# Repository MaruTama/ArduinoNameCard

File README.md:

# Arduino Name(Business) Card

[日本版 READE](./README_JP.md)  
This is a template with Arduino uno compatibility board.  
It is only one master, it is created with a business card size of 91 x 55 mm.  

If you wanna create as panelized boards, see the [twoBoards branch](https://github.com/MaruTama/ArduinoNameCard/tree/twoBoards) .  

This was written sample code(blink) with board.

# Environment version
- KiCad 5.0.0
- ArduinoIDE 1.8.2
- GIMP 2.8
- Ubuntu 16.04 and macOS High Sierra (my environment)

Basically, ArduinoIDE, KiCad, GIMP are cross-platform and do not depend on OS.  

# Environment construction method
## Installation of Arduino IDE
### windows
It is recommended to install with Chocolatey.  
because since installer took time to download from the official site.  

Installation of Chocolatey
["Chocolateyを使った環境構築の時のメモ"](https://qiita.com/konta220/items/95b40b4647a737cb51aa)
 please refer above.  

To open cmd or PowerShell with administrator privileges.  

```
> Chocolate Upgrade Chocolate
> Chocolate installation arduino
```

It is OK to response "Yes" that the question comes twice.  

Install the All drivers for Arduino.  

### Mac
Mac is using brew to install Arduino IDE

```
brew cask install arduino
```

### Ubuntu
["Here"](https://www.arduino.cc/en/Main/Software), download the latest Linux 32 or 64. zip.  
The installation method when downloaded file is arduino-1.8.2-linux64.tar.xz.  

```
$ sudo tar -Jxvf arduino-1.8.2-linux64.tar.xz -C /usr/share
$ cd /usr/share
$ sudo mv arduino-1.8.2/ arduino
# Create a symbolic link.
$ sudo ln -s /usr/share/arduino/arduino /usr/local/bin/arduino
# 実行
$ arduino
# Run it with administrator privileges when if you can not use the port.
$ sudo arduino
```

## Installation Kicad
### windows
#### Install with choco
To install with choco, execute the following commands.  

```
> choco upgrade chocolatey
> choco install kicad
```

### Install with Installer
If you are installing using the installer, download the installer from the official website below.  
[http://kicad-pcb.org/download/windows/](http://kicad-pcb.org/download/windows/)  

### Mac
If you are installing using the installer, download the installer from the official website below.  
"KiCad main package" is what component files puts the library in github.  
"KiCad extras" is what the component files puts the library in local directory.  
[http://kicad-pcb.org/download/osx/](http://kicad-pcb.org/download/osx/)  

### ubuntu
Execute the following commands.  

```
$ sudo add-apt-repository --yes ppa:js-reynaud/kicad-4
$ sudo apt update
$ sudo apt install kicad
```

## Setting of Kicad
### Component library
The component library is "~. Lib file".  
And each component is included in the file.  

Container Nebraska Pass

| Component library files | User defind search path |
|:------------|:--------------|
| res/lib/ArduinoNameCard.lib | res/lib |

### Footprint Library
The footprint library is a folder as a "~.Pretty".  
And contains the file ".kicad_mod" of each part footprint.  

Footprint library path  

| nickname | path |
|:------------|:--------------|
| ArduinoNameCard | ${KIPRJMOD}/res/lib/ArduinoNameCard.pretty |

### kicad library

Basically chip parts are unified to the following sizes.  

|   EIA  |   JIS  |
|:-------|:-------|
| 0805 | 2012 |

["Quick KICAD Library Component Builder"](http://kicad.rohrbacher.net/quicklib.php)
FT232RL.lib was created with above that using website.  

The ATMEGA 328-AU library was downloaded from ["here"](https://www.snapeda.com/parts/ATMEGA328-AU/Atmel/view-part/)

# # Build Arduino Name cards
Create a PCB footprint from the image.

### 1. Create an image according to the size of the free space on the Name Card
Create new image that using gimp.
Set about 1000dpi.  

The image used this time is put in [./res/img/origin](https://github.com/MaruTama/ArduinoNameCard/tree/master/res/img/origin) of the repository.
Please use this.  

Each image is supposed to write the following things.  
- affiliation.png -> affiliation
- name.png -> name
- address.png -> contact information

### 2. Enter pictures and characters in the picture
As an example, let's write the name in name.png.  
Binarize the image when if in case color image. -> 3  

### 3. I will make a black character white character
You need color turn when it's a white background and black character that  using gimp.  
how to turn color.  
menu -> "colors" -> "Inverted".  

### 4. Create a footprint
You can choose **silk** or **copper** what information to be placed on the board.  
If you put it in silk it will look like affiliation.png in the figure below.  
If it is copper, it will be like name.png and address.png.  

Start "bimmpa to component".  

To create a silk -> to 5  
To create a copper → to 6

### 5. Create with silk
Click "Load bitmap".  
As an example this time, I read name.png.  
Check sure the resolution is about 1000 dpi.  

Check "Front silk screen".  
Click "Export" after to generate output the filename.  
set name of output file as a name_silk.kicad_mod.  

### 6. Create with copper
Click "Load bitmap".  
As an example this time, I read name.png.  
Check sure the resolution is about 1000 dpi.  

Check "Front solder mask".  
Click "Export" after to generate output the filename.  
set name of output file as a name_mask.kicad_mod.   

Process the output footprint of name_mask.kicad_mod.  
In we will make that using the resist mask and the copper.  

The script is written in Python.  
A script is placed in [./python/main.py](https://github.com/MaruTama/ArduinoNameCard/blob/master/python/main.py) in the repository.  
Execute the following command to create a footprint.  

```
$ cd "Route of this project"
$ python python/main.py  res/lib/ArduinoNameCard.pretty/name_mask.kicad_mod
```

Then name_mask_and_cu.kicad_mod is generated.  

(If it is not generated, open name_cu.kicad_mod, copy the items included after "fp_ploy", replace "F.Mask" with "F.Cu", append the copied contents name_mask_and_cu. Please save it as kicad_mod.)  

### 7. Add a footprint to the library
Select ArduinoNameCard as the working library.  

Read the output file.  

Save the component in the library.  
If you are creating with silk, save it as "name_silk.kicad_mod".  
If you are using copper foil, save it as "name_mask_and_cu.kicad_mod".  

### 8. Installation on board
It's easiest to replace the existing footprint.  
Right click on the existing footprint.  
"Footprint exchange" -> "Footprint G *** ",  after opens the window.  

Press the footprint list and select the saved footprint.  

Press "Apply" to change the flip print.  

### 9. The solid filling of GND.
Click a red square place.  

Right click anywhere on the board and the following menu will appear.  
Select "Fill all zones" .  

This completes filling with solid of GND.

### 10. Confirmation
You can check it with 3D viewer in Menu -> "View" -> "3D viewer".  

# Order the board
### Creating Gerber data
How to create Gerber is that see this refer.  
[★kicad (Mac OSX Version: 4.0.5 release build)版でFusionPCB用ガーバーデータの作り方．](http://atmel.client.jp/fusionpcb.html).

Output gerver with "Menu" -> "file" -> "plot" .  

And output drill data.  

#### Rename Gerber datas
Rename gerver data to ArduinoNameCard.  

#### Create a zip of Gerber data
Export Compress every folder and put it in zip.  
Rename zip file name to ArduinoNameCard.  

### Placement order of board
You can check it by preview of seeed fusion.  
Select your favorite color.  

We will order the thickness of the board with **0.6 mm**.  

# Order parts
serial conversion part

| Parts | Number used for a board | rice at Akitsuki or DigKey |
|:------------|:--------------|:----------------|
| [FT230XS](http://akizukidenshi.com/catalog/g/gI-13311/)  | 1 | ¥220 |
| [1kΩ](http://akizukidenshi.com/catalog/g/gR-11796/)  | 2 | ¥100 |
| [0.1µF](http://akizukidenshi.com/catalog/g/gP-00355/)| 2 | ¥150 |
| [10µF](http://akizukidenshi.com/catalog/g/gP-07388/) | 1 | ¥150 |
| [Red LED](http://akizukidenshi.com/catalog/g/gI-06419/)| 1 | ¥150 |
| [Green LED](http://akizukidenshi.com/catalog/g/gI-06492/)| 1 | ¥150 |

Arduino compatible part

| Parts | Number used for a board | Price at Akitsuki or DigKey |
|:------------|:--------------|:----------------|
| [ATMEGA328P-AU](http://akizukidenshi.com/catalog/g/gI-04386/)  | 1 | ¥230 |
| [Oscillator 16MHz](http://akizukidenshi.com/catalog/g/gP-08671/) | 1 | ¥30 |
| [10kΩ](http://akizukidenshi.com/catalog/g/gR-11797/) | 1 | ¥100 |
| [1kΩ](http://akizukidenshi.com/catalog/g/gR-11796/)  | 2 | ¥100 |
| [330Ω](https://www.digikey.jp/product-detail/ja/stackpole-electronics-inc/RMCF0805JT330R/RMCF0805JT330RCT-ND/1942547) | 1 | ¥19 |
| [0.1µF](http://akizukidenshi.com/catalog/g/gP-00355/)| 1 | ¥150 |
|  [22pF](https://www.digikey.jp/product-detail/ja/murata-electronics-north-america/GRM21A5C2E220JW01D/490-5534-1-ND/2334930)          | 2 | ¥295 |
| [Hughes](http://akizukidenshi.com/catalog/g/gP-12636/)          | 1 | ¥200 |
| [Red LED](http://akizukidenshi.com/catalog/g/gI-06419/)| 1 | ¥150 |
| [Tact switch](http://akizukidenshi.com/catalog/g/gP-06185/) | 1 | ¥100 |

## Boot loader write
Write method with optifix.  
For the procedure,
please refer to ["【Arduino 1.6.3】 Arduino UnoでATmega328P-PUにブートローダを書き込む"](http://ijmp320.hatenablog.jp/entry/2015/05/16/121922)

flashing before soldering using ["IC socket"](http://www.aitendo.com/product/15796).  

Connect Arduino UNO and ATMEGA 328P-AU with the following combination.  

| Arduino UNO | ATMEGA328P-AU | Location on card (board) |
|:------------|:--------------|:----------------|
| D10 (SS)    | 29 (RESET)    | RST |
| D11 (MOSI)  | 15 (MOSI)     | D11 |
| D12 (MISO)  | 16 (MISO)     | D12 |
| D13 (SCK)   | 17 (SCK)      | D13 |
| 5V          | 4 or 6        | 5V  |
| GND         | 3 or 5        | GND |

## Soldering
FT232RL is narrow between pins and it's difficult to solder.  
Although soldering can be done normally, I recommend that you follow the procedure below.  

### 1. Apply more flux.

### 2. Add a light solder to the land first.

### 3. Align the feet, fix it by applying a soldering iron from the top.

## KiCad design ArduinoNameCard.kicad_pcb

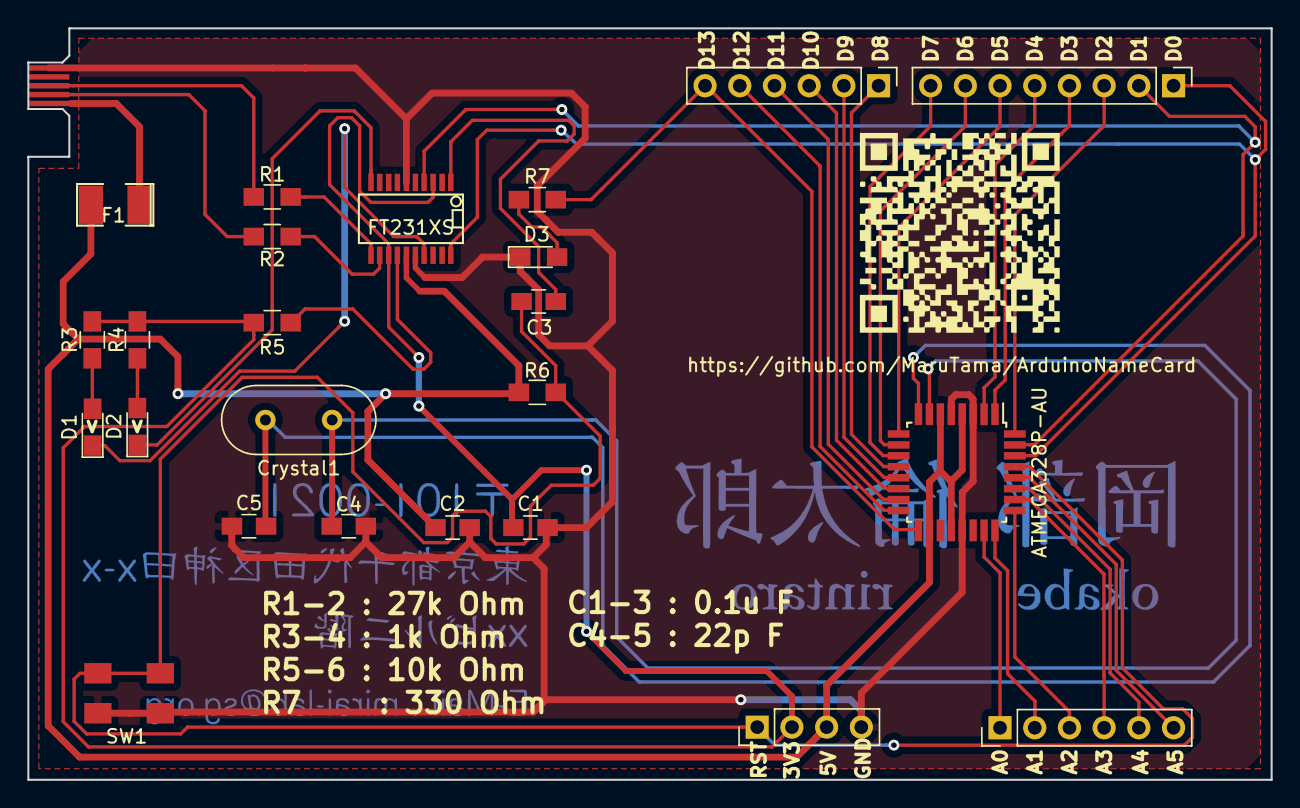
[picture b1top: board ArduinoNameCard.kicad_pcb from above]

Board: 2 copper layers, 91.0 x 55.0 mm, 25 parts (0 on the bottom side), 38 nets.

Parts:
ATMEGA328P-AU: MCU-ATMEGA328P-AU(TQFP32); TQFP-32_7x7mm_Pitch0.8mm
C1, C2, C3: 0.1u; C_0805_HandSoldering
C4, C5: 22p; C_0805_HandSoldering
Crystal1: 16MHz; Crystal_HC49-U_Vertical
D1: RED(TX); LED_0805_HandSoldering
D2: GREEN(RX); LED_0805_HandSoldering
D3: RED; LED_0805_HandSoldering
F1: 500mA; SMD-1210_Pol
FT231XS: FT231XS; SSOP-20
J1: USB_B_Micro; namecard_microB
J2: Conn_01x04; Socket_Strip_Straight_1x04_Pitch2.54mm
J3, J5: Conn_01x06; Pin_Header_Straight_1x06_Pitch2.54mm
J4: Conn_01x08; Pin_Header_Straight_1x08_Pitch2.54mm
R1, R2: 27; R_0805_HandSoldering
R3, R4: 1k; R_0805_HandSoldering
R5, R6: 10k; R_0805_HandSoldering
R7: 330; R_0805_HandSoldering
SW1: SW_Push; switch_4632

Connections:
3V3: C1.1, FT231XS.3, FT231XS.13, J2.2, R3.1, R4.1, R5.1
5V: ATMEGA328P-AU.4, ATMEGA328P-AU.6, ATMEGA328P-AU.18, ATMEGA328P-AU.20, C2.1, F1.2, FT231XS.15, J2.3, R6.1
+5V: F1.1, J1.1
D+: FT231XS.11, R1.1
D-: FT231XS.12, R2.2
DTR: ATMEGA328P-AU.29, C3.1, J2.1, R6.2, SW1.1
GND: ATMEGA328P-AU.3, ATMEGA328P-AU.5, ATMEGA328P-AU.21, C1.2, C2.2, C4.2, C5.2, D3.1, FT231XS.6, FT231XS.16, J1.5, J2.4, SW1.2
unnamed: C3.2, FT231XS.1
unnamed: ATMEGA328P-AU.7, C4.1, Crystal1.1
unnamed: ATMEGA328P-AU.8, C5.1, Crystal1.2
unnamed: D1.1, FT231XS.17
unnamed: D1.2, R3.2
unnamed: D2.1, FT231XS.10
unnamed: D2.2, R4.2
unnamed: D3.2, R7.1
unnamed: J1.2, R2.1
unnamed: J1.3, R1.2
unnamed: ATMEGA328P-AU.23, J3.1
unnamed: ATMEGA328P-AU.24, J3.2
unnamed: ATMEGA328P-AU.25, J3.3
unnamed: ATMEGA328P-AU.26, J3.4
unnamed: ATMEGA328P-AU.27, J3.5
unnamed: ATMEGA328P-AU.28, J3.6
unnamed: ATMEGA328P-AU.32, J4.3
unnamed: ATMEGA328P-AU.1, J4.4
unnamed: ATMEGA328P-AU.2, J4.5
unnamed: ATMEGA328P-AU.9, J4.6
unnamed: ATMEGA328P-AU.10, J4.7
unnamed: ATMEGA328P-AU.11, J4.8
unnamed: ATMEGA328P-AU.12, J5.1
unnamed: ATMEGA328P-AU.13, J5.2
unnamed: ATMEGA328P-AU.14, J5.3
unnamed: ATMEGA328P-AU.15, J5.4
unnamed: ATMEGA328P-AU.16, J5.5
unnamed: ATMEGA328P-AU.17, J5.6, R7.2
unnamed: FT231XS.14, R5.2
RX: ATMEGA328P-AU.31, FT231XS.4, J4.2
TX: ATMEGA328P-AU.30, FT231XS.20, J4.1

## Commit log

2018-04-07 ・README.mdの追加 ・PCBの設計 諸変更を行った。
2018-04-08 ・READMEの更新 ・PCBの完成
2018-04-08 READMEに加筆した
2018-04-08 ・枠外にviaが残っていたので削除 ・回路図のpdfを追加
2018-04-08 READMEの修正
2018-04-14 回路にヒューズを追加した
2018-04-14 LEDの種類に関する追記 部品のパラメータのシルクの追加
2018-04-14 READMEの追加
2018-04-14 Update LICENSE
2018-04-14 電源配線幅を拡張した
2018-04-19 ・DRCで配線幅についてエラーが出ていたので修正した ・R5のシルクの位置を上付きに修正した
2018-04-24 ・READMEに記載している部品を変更した ・端子部分のベタGNDは不要（厚くなる）なので削除した
2018-04-25 LEDに向きのシルクを追加
2018-04-25 面付け用のボードを作成した
2018-05-02 ・面付基板でのPCB作成方法の追記 ・実物写真の追加 ・銅箔フットプリント作成のpyhtonスクリプトの追加
2018-05-02 銅箔フットプリントの作成方法を更新した フットプリントの置換方法を追記した
2018-05-02 REAMEの更新
2018-05-02 READMEの基板の厚みを修正
2018-05-02 READMEでの更新
2018-05-02 PCBのmicroBのフットプリントが存在しないものを参照していたので修正
2018-05-09 READMEの修正と動作gifを
2018-05-09 READMEの修正と動作gifの追加
2018-05-09 gifを忘れてたので追加
2018-06-03 画像の縮小とREADMEへICのはんだ付け手順を追記した
2018-06-03 画像が間違っていたので、差し替えた
2018-08-09 README の英語版の準備のために、日本語版を別ファイルで作成した。
2018-08-09 READMEに改行を追加した
2018-08-11 英語版のREADMEを書いた
2018-08-11 また、READMEの修正
2018-08-11 READMEの表が崩れてたので修正した
2018-08-11 README の gif が動かなかったのでパスを修正
2019-02-15 https://github.com/DroidDIY/FT230XBreakout を参考にFT230XSに書き換えた。
2019-02-17 FT232RLをFT230XSに置き換えた。
2019-02-17 githubのQRコードを追加した。
2019-02-17 とりあえず、実動したら、twoBoardブランチにも実装する
2019-05-18 FT231Xに変更した。
2019-06-23 部品の並びなどを修正した。
